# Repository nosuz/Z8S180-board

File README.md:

# Z80(Z8S180) CPU board

This board is designed for running CP/M.

|item|spec|
|:--|:--|
|CPU|Z8S180|
|CPU Clock|Max. 16MHz|
|Memory|128KiB|
|Interface|USB|

The USB port is used as a interface to connect with the subsystem that controles a console and disk drives.

|File name|Contents|
|:---------|:---|
|Z8S180.pdf|Circuit drawing(PDF)|
|Z8S180.xlsx|BOM list(Excel)|
|Z8S180.zip|zipped Gerber files|

## References

[Z80マイコンボードの製作](https://tech.nosuz.jp/2016/08/z80-cpu-borad/)

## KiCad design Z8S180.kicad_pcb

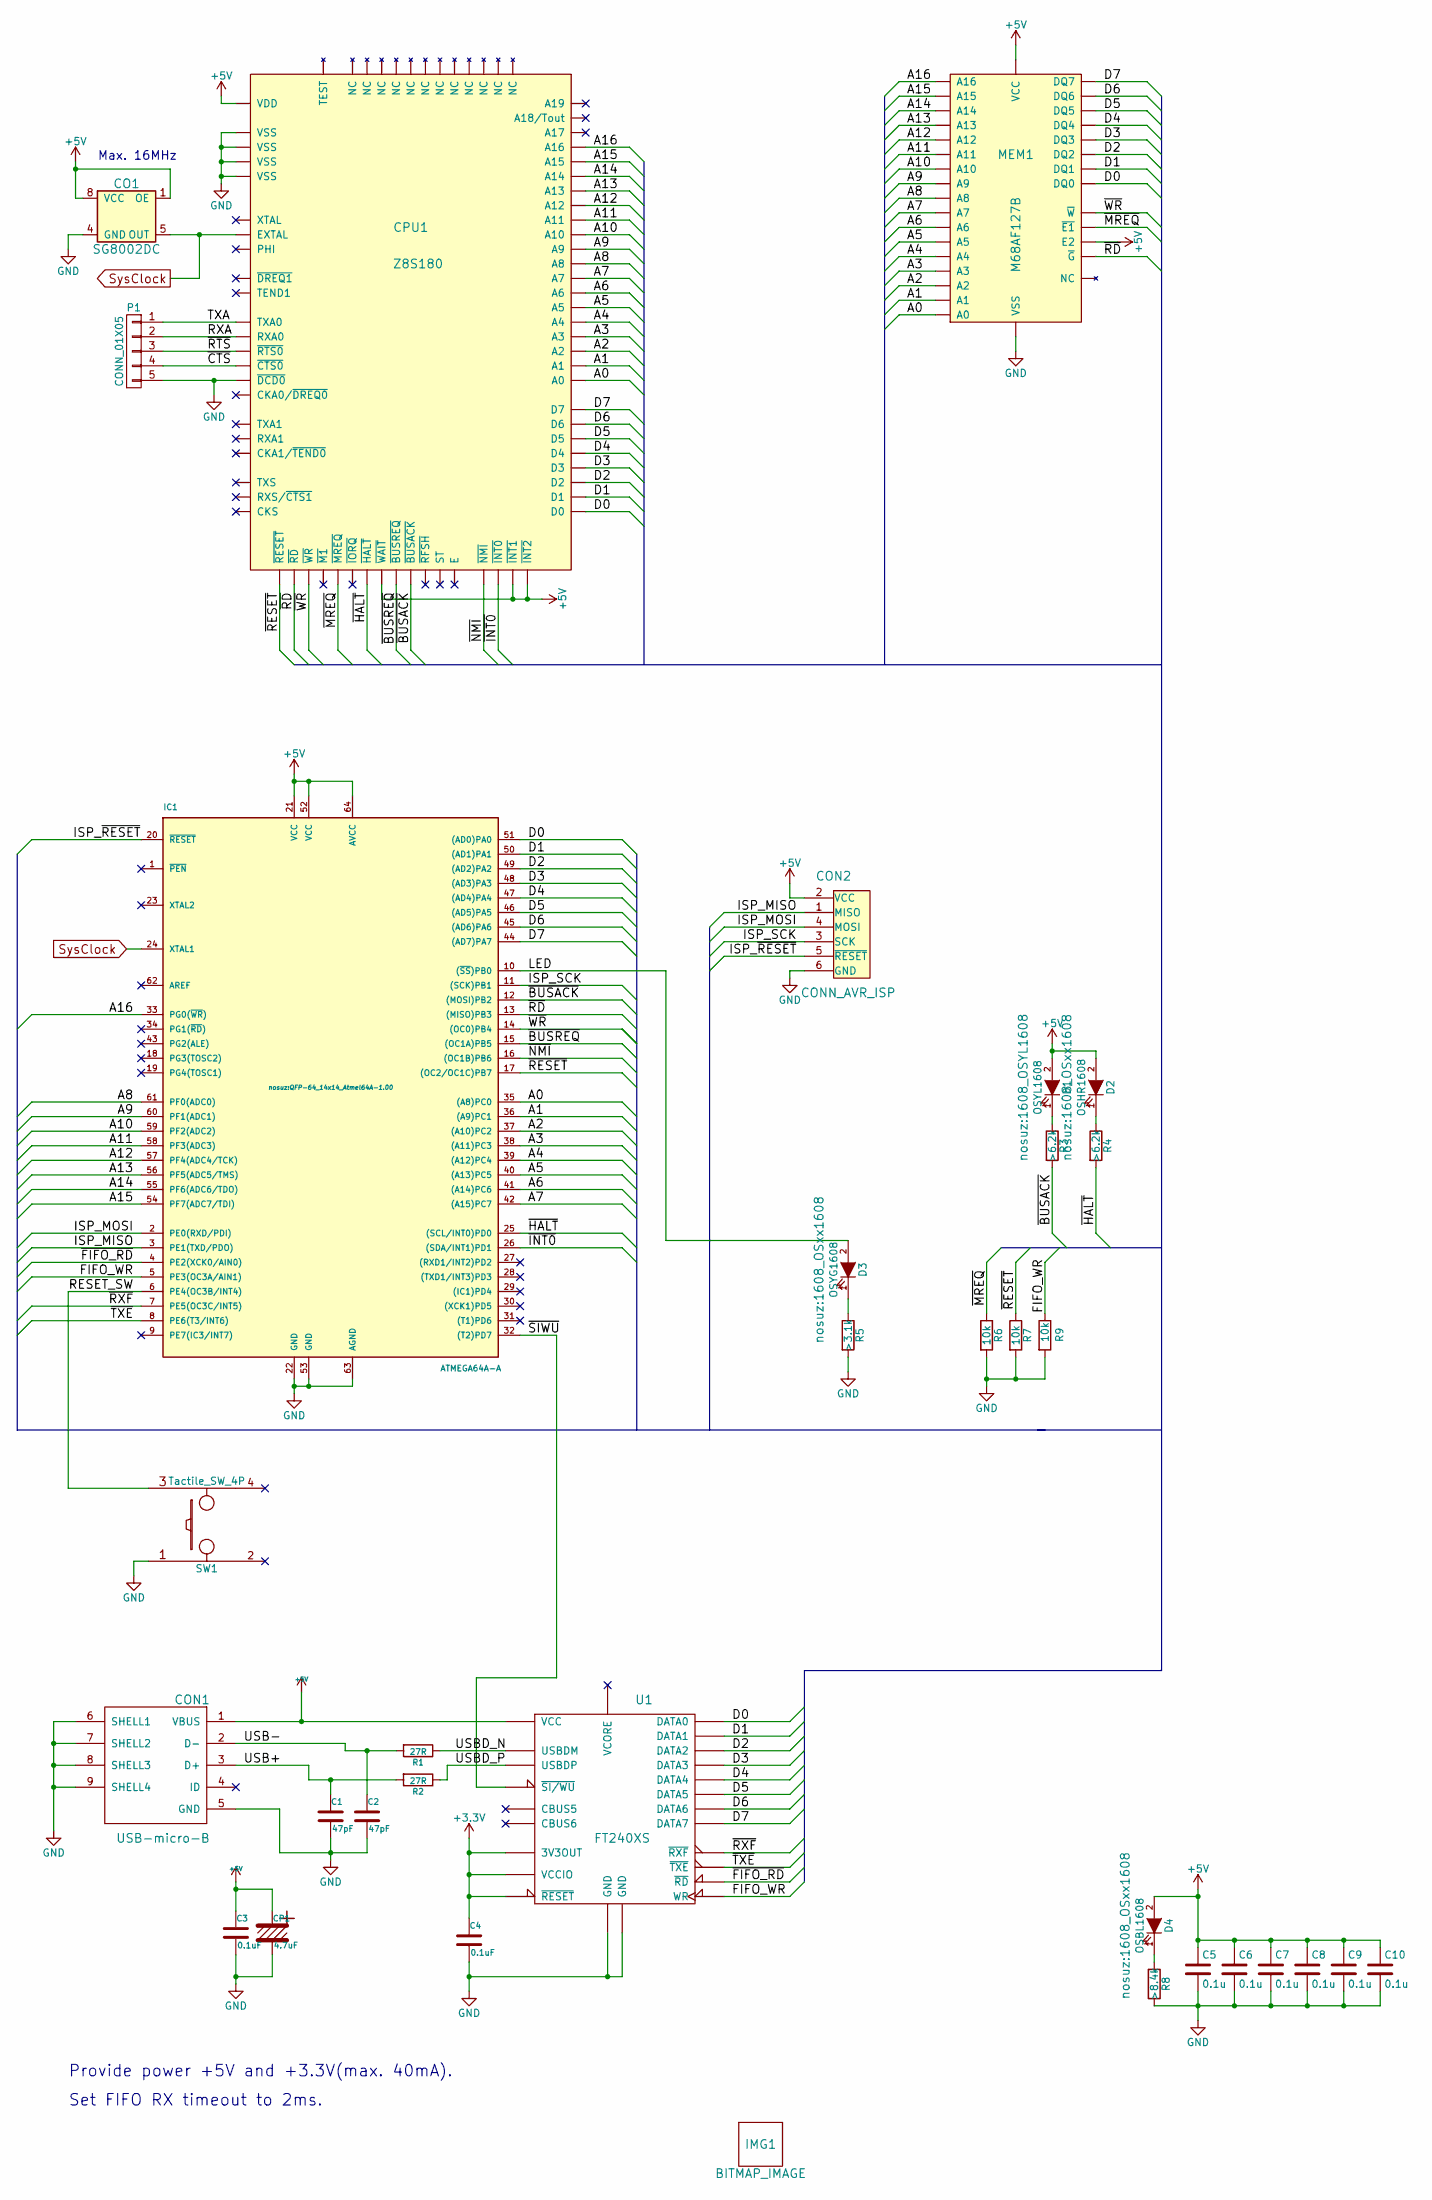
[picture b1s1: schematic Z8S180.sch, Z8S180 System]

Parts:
C1, C2: 47pF; C_2012
C3, C4: 0.1uF; C_2012
C5, C6, C7, C8, C9, C10: 0.1u; C_2012
CO1: SG8002DC; DIP8_2227MC-08
CON1: USB-micro-B; USB-micro-B_Hirose
CON2: CONN_AVR_ISP; AVR_ISP_2x03
CP1: 4.7uF; CP_SMD_D5
CPU1: Z8S180; QFP80_Z8S180
D1: OSYL1608; 1608_OSYL1608
D2: OSHR1608; 1608_OSxx1608
D3: OSYG1608; 1608_OSxx1608
D4: OSBL1608; 1608_OSxx1608
IC1: ATMEGA64A-A; QFP-64_14x14_Atmel64A-1.00
IMG1: BITMAP_IMAGE; Icon_Nosuz
MEM1: M68AF127B; SO32_STM_M68AF127B
P1: CONN_01X05; Pin_Header_Straight_1x05
R1, R2: 27R; R_1608
R3, R4: >6.2k; R_1608
R5: >3.1k; R_1608
R6, R7, R9: 10k; R_1608
R8: >8.4k; R_1608
SW1: Tactile_SW_4P; SKRPACE010
U1: FT240XS; SSOP-24_FT240XS

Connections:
+3V3: C4.1, U1.3 (VCCIO), U1.15 (3V3OUT), U1.16 (~RESET)
+5V: C3.1, C5.1, C6.1, C7.1, C8.1, C9.1, C10.1, CO1.1 (OE), CO1.8 (VCC), CON1.1 (VBUS), CON2.2 (VCC), CP1.1, CPU1.5 (~INT1), CPU1.6 (~INT2), CPU1.32 (VDD), CPU1.77 (~WAIT), D1.2 (A), D2.2 (A), D4.2 (A), IC1.21 (VCC), IC1.52 (VCC), IC1.64 (AVCC), MEM1.30 (E2), MEM1.32 (VCC), U1.18 (VCC)
/A0: CPU1.8 (A0), IC1.35 ((A8)PC0), MEM1.12 (A0)
/A1: CPU1.9 (A1), IC1.36 ((A9)PC1), MEM1.11 (A1)
/A2: CPU1.10 (A2), IC1.37 ((A10)PC2), MEM1.10 (A2)
/A3: CPU1.11 (A3), IC1.38 ((A11)PC3), MEM1.9 (A3)
/A4: CPU1.13 (A4), IC1.39 ((A12)PC4), MEM1.8 (A4)
/A5: CPU1.15 (A5), IC1.40 ((A13)PC5), MEM1.7 (A5)
/A6: CPU1.16 (A6), IC1.41 ((A14)PC6), MEM1.6 (A6)
/A7: CPU1.17 (A7), IC1.42 ((A15)PC7), MEM1.5 (A7)
/A8: CPU1.18 (A8), IC1.61 (PF0(ADC0)), MEM1.27 (A8)
/A9: CPU1.19 (A9), IC1.60 (PF1(ADC1)), MEM1.26 (A9)
/A10: CPU1.20 (A10), IC1.59 (PF2(ADC2)), MEM1.23 (A10)
/A11: CPU1.21 (A11), IC1.58 (PF3(ADC3)), MEM1.25 (A11)
/A12: CPU1.24 (A12), IC1.57 (PF4(ADC4/TCK)), MEM1.4 (A12)
/A13: CPU1.25 (A13), IC1.56 (PF5(ADC5/TMS)), MEM1.28 (A13)
/A14: CPU1.26 (A14), IC1.55 (PF6(ADC6/TDO)), MEM1.3 (A14)
/A15: CPU1.27 (A15), IC1.54 (PF7(ADC7/TDI)), MEM1.31 (A15)
/A16: CPU1.28 (A16), IC1.33 (PG0(~WR~)), MEM1.2 (A16)
/D0: CPU1.35 (D0), IC1.51 ((AD0)PA0), MEM1.13 (DQ0), U1.24 (DATA0)
/D1: CPU1.36 (D1), IC1.50 ((AD1)PA1), MEM1.14 (DQ1), U1.4 (DATA1)
/D2: CPU1.37 (D2), IC1.49 ((AD2)PA2), MEM1.15 (DQ2), U1.2 (DATA2)
/D3: CPU1.38 (D3), IC1.48 ((AD3)PA3), MEM1.17 (DQ3), U1.9 (DATA3)
/D4: CPU1.39 (D4), IC1.47 ((AD4)PA4), MEM1.18 (DQ4), U1.1 (DATA4)
/D5: CPU1.40 (D5), IC1.46 ((AD5)PA5), MEM1.19 (DQ5), U1.7 (DATA5)
/D6: CPU1.41 (D6), IC1.45 ((AD6)PA6), MEM1.20 (DQ6), U1.8 (DATA6)
/D7: CPU1.44 (D7), IC1.44 ((AD7)PA7), MEM1.21 (DQ7), U1.5 (DATA7)
/FIFO_WR: IC1.5 (PE3(OC3A/AIN1)), R9.1, U1.12 (WR)
/ISP_MISO: CON2.1 (MISO), IC1.3 (PE1(TXD/PDO))
/ISP_MOSI: CON2.4 (MOSI), IC1.2 (PE0(RXD/PDI))
/ISP_SCK: CON2.3 (SCK), IC1.11 ((SCK)PB1)
/ISP_~RESET: CON2.5 (~RESET), IC1.20 (~RESET)
/LED: D3.2 (A), IC1.10 ((~SS~)PB0)
/RESET_SW: IC1.6 (PE4(OC3B/INT4)), SW1.3
/RXA: CPU1.49 (RXA0), P1.2
/TXA: CPU1.48 (TXA0), P1.1
/USB+: C1.1, CON1.3 (D+), R2.2
/USB-: C2.1, CON1.2 (D-), R1.2
/USBD_N: R1.1, U1.14 (USBDM)
/USBD_P: R2.1, U1.13 (USBDP)
/~BUSACK: CPU1.78 (~BUSACK), IC1.12 ((MOSI)PB2), R3.2
/~BUSREQ: CPU1.79 (~BUSREQ), IC1.15 ((OC1A)PB5)
/~CTS: CPU1.46 (~CTS0), P1.4
/~FIFO_RD: IC1.4 (PE2(XCK0/AIN0)), U1.11 (~RD)
/~HALT: CPU1.61 (~HALT), IC1.25 ((SCL/INT0)PD0), R4.2
/~INT0: CPU1.4 (~INT0), IC1.26 ((SDA/INT1)PD1)
/~MREQ: CPU1.66 (~MREQ), MEM1.22 (~E1), R6.1
/~NMI: CPU1.1 (~NMI), IC1.16 ((OC1B)PB6)
/~RD: CPU1.70 (~RD), IC1.13 ((MISO)PB3), MEM1.24 (~G)
/~RESET: CPU1.80 (~RESET), IC1.17 ((OC2/OC1C)PB7), R7.1
/~RTS: CPU1.45 (~RTS0), P1.3
/~RXF: IC1.7 (PE5(OC3C/INT5)), U1.21 (~RXF)
/~SIWU: IC1.32 ((T2)PD7), U1.10 (~SI/WU)
/~TXE: IC1.8 (PE6(T3/INT6)), U1.20 (~TXE)
/~WR: CPU1.69 (~WR), IC1.14 ((OC0)PB4), MEM1.29 (~W)
GND: C1.2, C2.2, C3.2, C4.2, C5.2, C6.2, C7.2, C8.2, C9.2, C10.2, CO1.4 (GND), CON1.5 (GND), CON1.6 (SHELL1), CON1.7 (SHELL2), CON1.8 (SHELL3), CON1.9 (SHELL4), CON2.6 (GND), CP1.2, CPU1.12 (VSS), CPU1.34 (VSS), CPU1.47 (~DCD0), CPU1.72 (VSS), CPU1.73 (VSS), IC1.22 (GND), IC1.53 (GND), IC1.63 (AGND), MEM1.16 (VSS), P1.5, R5.2, R6.2, R7.2, R8.2, R9.2, SW1.1, U1.6 (GND), U1.19 (GND)
unnamed: D1.1 (K), R3.1
unnamed: D2.1 (K), R4.1
unnamed: D3.1 (K), R5.1
unnamed: D4.1 (K), R8.1
SysClock: CO1.5 (OUT), CPU1.76 (EXTAL), IC1.24 (XTAL1)

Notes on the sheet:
Provide power +5V and +3.3V(max. 40mA).
Set FIFO RX timeout to 2ms.
Max. 16MHz

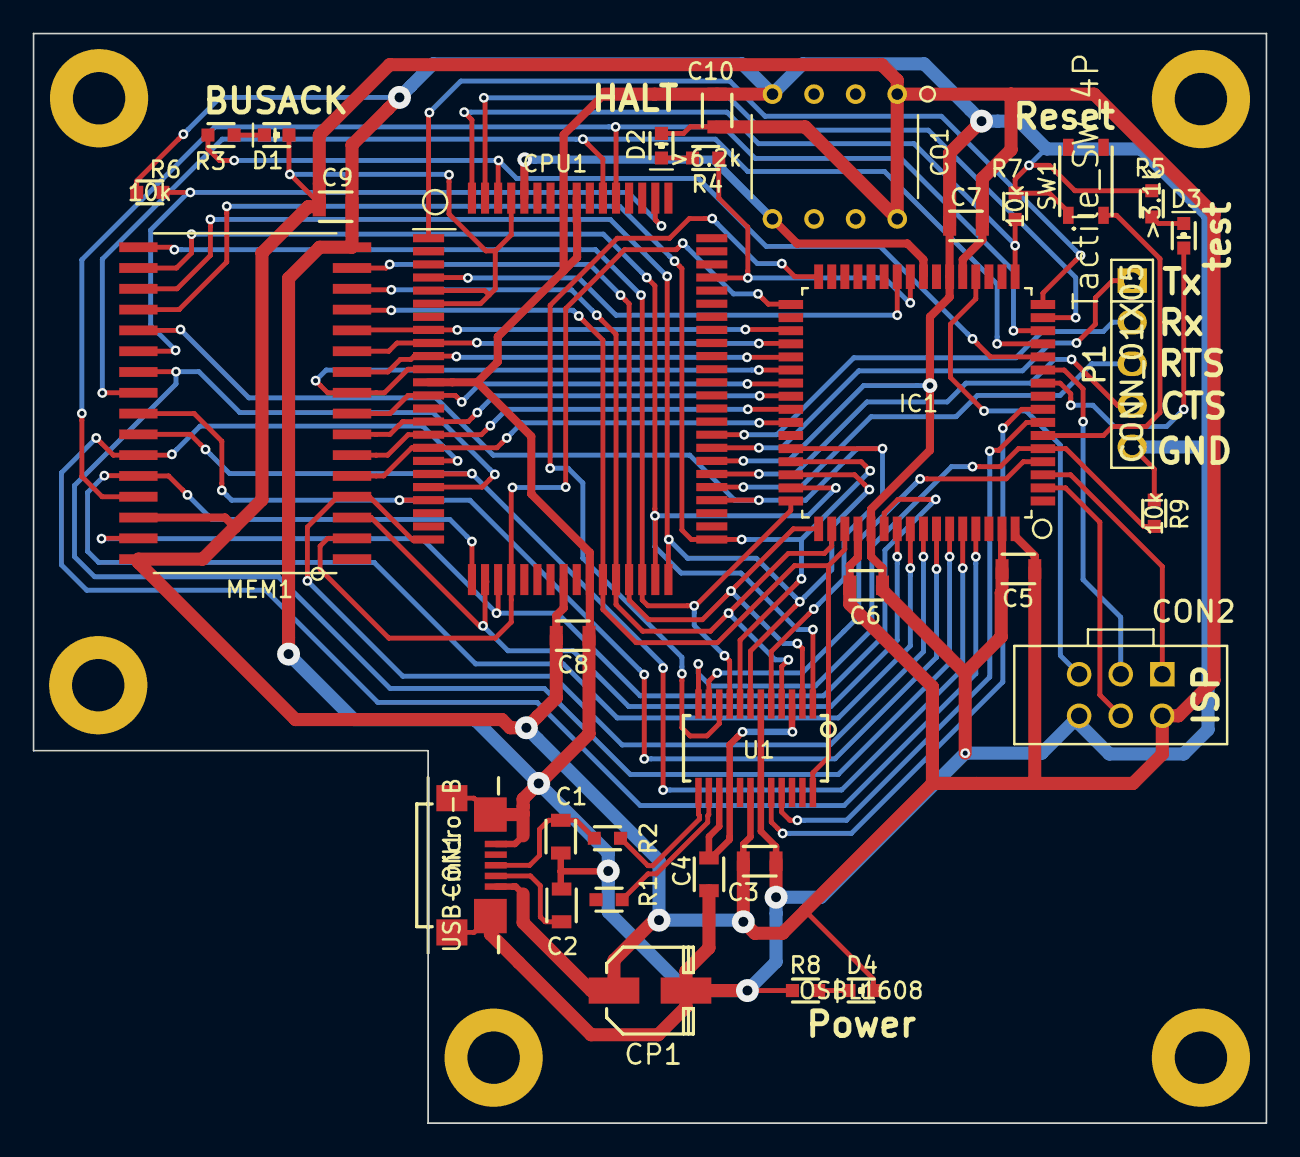
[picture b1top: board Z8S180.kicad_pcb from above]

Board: 2 copper layers, 75.3 x 66.6 mm, 34 parts (1 on the bottom side), 61 nets.

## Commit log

2016-08-24 Added a components file.
2016-08-24 Added README files
2016-08-24 Fixed wrong file names: README.md and README-ja.md
2016-08-24 Fixed README table header
